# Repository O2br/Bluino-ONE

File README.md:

# Bluino-ONE
Schematics and PCB eagle Bluino-ONE

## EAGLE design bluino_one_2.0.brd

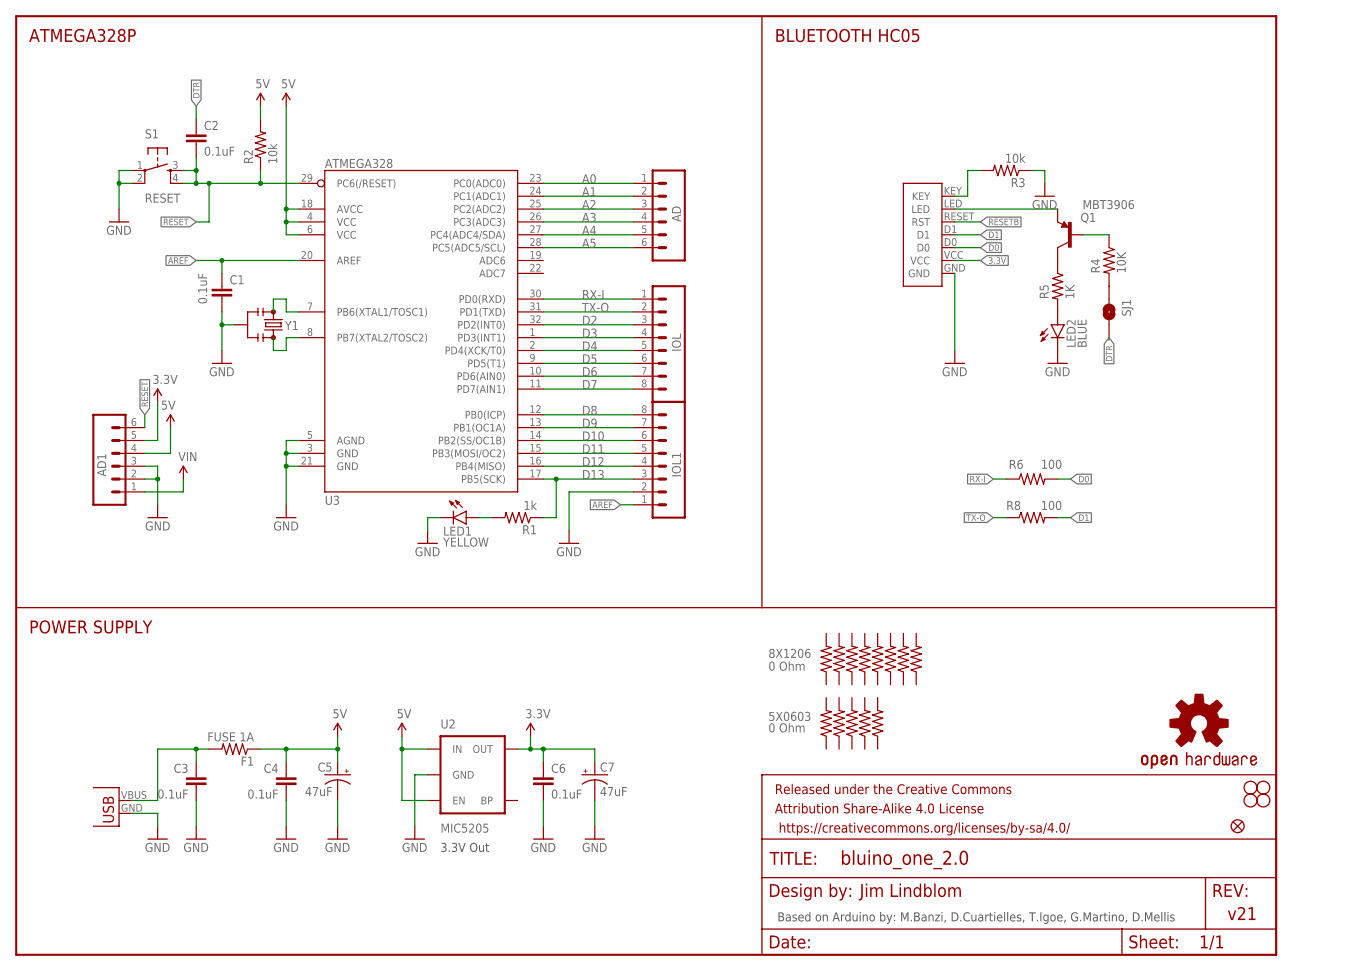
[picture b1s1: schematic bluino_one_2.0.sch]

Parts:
5X0603: 0 Ohm; 0603-RES-JUMP
8X1206: 0 Ohm; 1206-JUMP
AD, AD1: M06SMD-STRAIGHT-COMBO; 1X06_SMD_STRAIGHT_COMBO
C1, C2, C3, C4: 0.1uF; 0603-CAP
C5, C7: 47uF; EIA3216
C6: 0.1uF; 0603-CAP-JUMP
F1: FUSE 1A; 1206-JUMP
FID1: FIDUCIAL1.5X3; FIDUCIAL-1.5X3
FRAME2: FRAME-LETTER; CREATIVE_COMMONS
IOL, IOL1: M08SMD-COMBO; 1X08_SMD_COMBINED
JP3, JP4, JP5, JP6: STAND-OFF
LED1: YELLOW; LED-0603
LED2: BLUE; LED-0603
Q1: MBT3906; SOT23-3
R1: 1k; 0603-RES
R2: 10k; 0603-RES
R3, R15, R17, R18, R19: 10k; 0603-RES-JUMP
R4: 10K; 0603-RES
R5: 1K; 0603-RES
R6: 100; 0603-RES
R8: 100; 0603-RES-JUMP
R10, R11, R12, R51, R61, R71: 10k; 1206-JUMP
R41: 0; 1206-JUMP
S1: RESET; TACTILE_SWITCH_SMD
SJ1: SPARKFUN22_SOLDERJUMPERNC; SPARKFUN22_SJ_2S
U2: MIC5205; SOT23-5
U3: ATMEGA328; TQFP32-08
U$9: HC05_KEY; BLUINO_ONE_HC05
U$16: OSHW-LOGOS; OSHW-LOGO-S
X1: USB-MICROB; USB_SOCKET
Y1: 8MHZ; RESONATOR-SMD

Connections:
3.3V: AD1.5, C6.1, C7.A (+), U2.5 (OUT), U$9.VCC
5V: AD1.4, C4.1, C5.A (+), F1.1, R2.2, U2.1 (IN), U2.3 (EN), U3.4 (VCC), U3.6 (VCC), U3.18 (AVCC)
A0: AD.1, U3.23 (PC0(ADC0))
A1: AD.2, U3.24 (PC1(ADC1))
A2: AD.3, U3.25 (PC2(ADC2))
A3: AD.4, U3.26 (PC3(ADC3))
A4: AD.5, U3.27 (PC4(ADC4/SDA))
A5: AD.6, U3.28 (PC5(ADC5/SCL))
AREF: C1.1, IOL1.1, U3.20 (AREF)
D0: R6.2, U$9.D0
D1: R8.2, U$9.D1
D2: IOL.3, U3.32 (PD2(INT0))
D3: IOL.4, U3.1 (PD3(INT1))
D4: IOL.5, U3.2 (PD4(XCK/T0))
D5: IOL.6, U3.9 (PD5(T1))
D6: IOL.7, U3.10 (PD6(AIN0))
D7: IOL.8, U3.11 (PD7(AIN1))
D8: IOL1.8, U3.12 (PB0(ICP))
D9: IOL1.7, U3.13 (PB1(OC1A))
D10: IOL1.6, U3.14 (PB2(SS/OC1B))
D11: IOL1.5, U3.15 (PB3(MOSI/OC2))
D12: IOL1.4, U3.16 (PB4(MISO))
D13: IOL1.3, R1.1, U3.17 (PB5(SCK))
DTR: C2.1, SJ1.2
GND: AD1.2, AD1.3, C1.2, C3.2, C4.2, C5.C (-), C6.2, C7.C (-), IOL1.2, LED1.C, LED2.C, R3.1, S1.1, S1.2, U2.2 (GND), U3.3 (GND), U3.5 (AGND), U3.21 (GND), U$9.GND, X1.GND, Y1.2
LED: Q1.2 (E), U$9.LED
unnamed: LED1.A, R1.2
unnamed: R3.2, U$9.KEY
unnamed: U3.7 (PB6(XTAL1/TOSC1)), Y1.1
unnamed: U3.8 (PB7(XTAL2/TOSC2)), Y1.3
unnamed: Q1.3 (C), R5.1
unnamed: LED2.A, R5.2
unnamed: Q1.1 (B), R4.1
RESET: AD1.6, C2.2, R2.1, S1.3, S1.4, U3.29 (PC6(/RESET))
RESETB: R4.2, SJ1.1, U$9.RESET (RST)
RX-I: IOL.1, R6.1, U3.30 (PD0(RXD))
TX-O: IOL.2, R8.1, U3.31 (PD1(TXD))
VIN: AD1.1
VUSB: C3.1, F1.2, X1.VBUS

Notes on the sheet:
BLUETOOTH HC05
ATMEGA328P
POWER SUPPLY
Based on Arduino by: M.Banzi, D.Cuartielles, T.Igoe, G.Martino, D.Mellis
3.3V Out
Jim Lindblom
v21

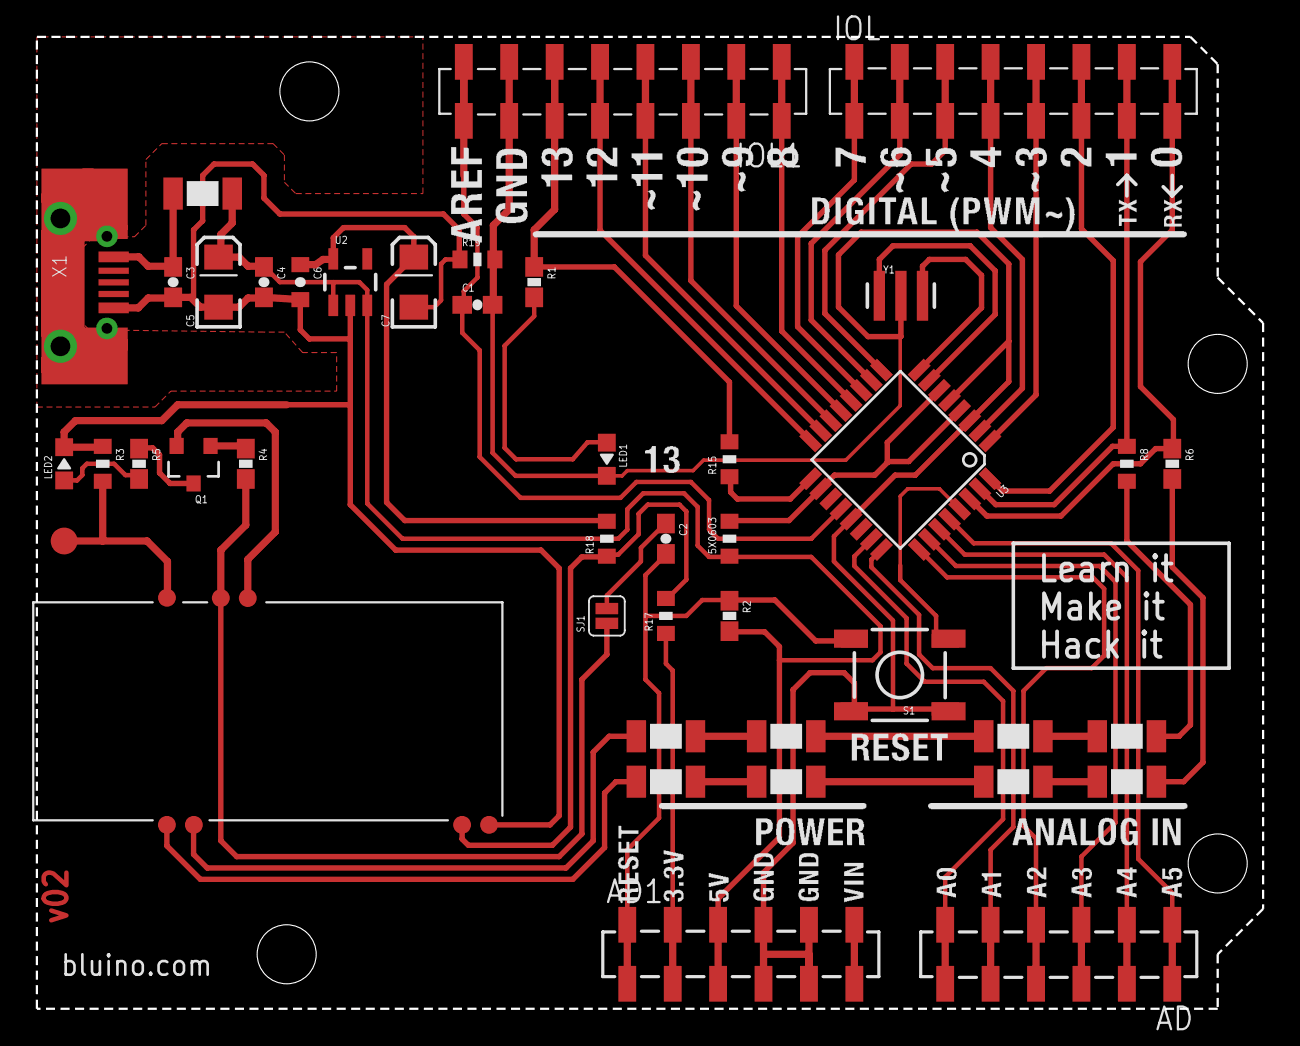
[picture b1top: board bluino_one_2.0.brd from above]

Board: 2 copper layers, 68.6 x 54.4 mm, 49 parts (1 on the bottom side), 38 nets.

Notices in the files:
parts and their libraries:
SparkFun-Aesthetics: Licensing: CC v3.0 Share-Alike You are welcome to use this library for commercial purposes.
SparkFun-Aesthetics: Released under the Creative Commons Attribution Share-Alike 4.0 License
SparkFun-Aesthetics: https://creativecommons.org/licenses/by-sa/4.0
